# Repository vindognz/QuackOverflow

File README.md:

# QuackOverflow

A wirelessly-charged LED rubber duck for debugging. Custom PCB with RGB LEDs and rechargeable battery fits inside a Kmart duck. Charges on a 3D-printed "DEBUGGING IN PROGRESS" stand. Because explaining your code to a glowing duck is more fun than regular rubber duck debugging.

## Features
- 5x RGB LEDs
- Wireless Qi charging
- Auto-sleep when on charging pad
- Low battery warning (red flash)
- Custom PCB fits inside $2 Kmart duck

## Hardware
- ESP32-C3 microcontroller
- WS2812B RGB LEDs
- LiPo battery with Qi charging
- Custom PCB
- 3D printed charging base

## The Story
Rubber duck debugging is a real technique where programmers explain their code line-by-line to an inanimate object (traditionally a rubber duck) to help spot bugs. I was gifted this duck as a coding companion for my birthday. I always imagined it glowing for those 2am debugging sessions. This project aims to make that dream a reality.

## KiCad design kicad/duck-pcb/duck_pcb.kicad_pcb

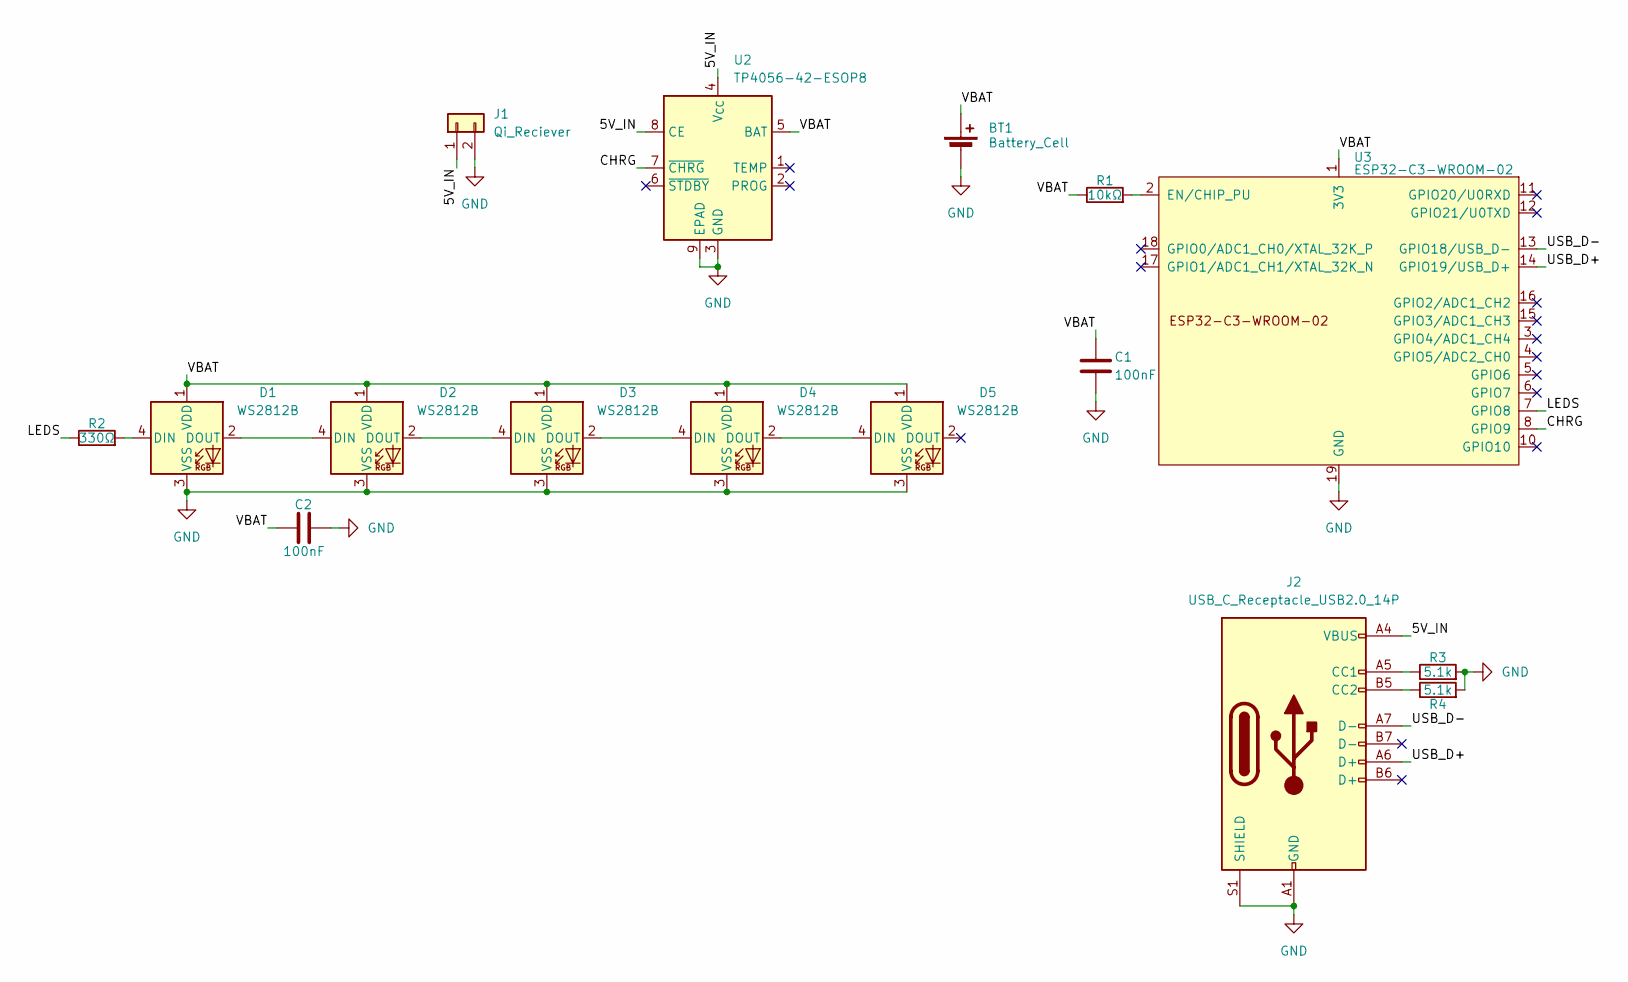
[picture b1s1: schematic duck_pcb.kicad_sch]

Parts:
BT1: Battery_Cell; PinHeader_1x02_P1.00mm_Vertical
C1, C2: 100nF; C_1206_3216Metric_Pad1.33x1.80mm_HandSolder
D1, D2, D3, D4, D5: WS2812B; LED_WS2812B_PLCC4_5.0x5.0mm_P3.2mm
J1: Qi_Reciever; PinHeader_1x02_P1.00mm_Vertical
J2: USB_C_Receptacle_USB2.0_14P; USB_C_Receptacle_HRO_TYPE-C-31-M-12
R1: 10kΩ; R_1206_3216Metric_Pad1.30x1.75mm_HandSolder
R2: 330Ω; R_1206_3216Metric_Pad1.30x1.75mm_HandSolder
R3, R4: 5.1k; R_1206_3216Metric_Pad1.30x1.75mm_HandSolder
U2: TP4056-42-ESOP8; SOIC-8-1EP_3.9x4.9mm_P1.27mm_EP2.41x3.3mm_ThermalVias
U3: ESP32-C3-WROOM-02

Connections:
/5V_IN: J1.1, J2.A4 (VBUS), J2.A9 (VBUS), J2.B4 (VBUS), J2.B9 (VBUS), U2.4 (V_{CC}), U2.8 (CE)
/CHRG: U2.7 (~CHRG), U3.8 (GPIO9)
/LEDS: R2.1, U3.7 (GPIO8)
/USB_D+: J2.A6 (D+), U3.14 (GPIO19/USB_D+)
/USB_D-: J2.A7 (D-), U3.13 (GPIO18/USB_D-)
/VBAT: BT1.1 (+), C1.1, C2.1, D1.1 (VDD), D2.1 (VDD), D3.1 (VDD), D4.1 (VDD), D5.1 (VDD), R1.1, U2.5 (BAT), U3.1 (3V3)
GND: BT1.2 (-), C1.2, C2.2, D1.3 (VSS), D2.3 (VSS), D3.3 (VSS), D4.3 (VSS), D5.3 (VSS), J1.2, J2.A1 (GND), J2.A12 (GND), J2.B1 (GND), J2.B12 (GND), J2.S1 (SHIELD), R3.2, R4.2, U2.3 (GND), U2.9 (EPAD), U3.9 (GND), U3.19 (GND)
unnamed: D1.4 (DIN), R2.2
unnamed: D1.2 (DOUT), D2.4 (DIN)
unnamed: D2.2 (DOUT), D3.4 (DIN)
unnamed: D3.2 (DOUT), D4.4 (DIN)
unnamed: D4.2 (DOUT), D5.4 (DIN)
unnamed: J2.A5 (CC1), R3.1
unnamed: J2.B5 (CC2), R4.1
unnamed: R1.2, U3.2 (EN/CHIP_PU)

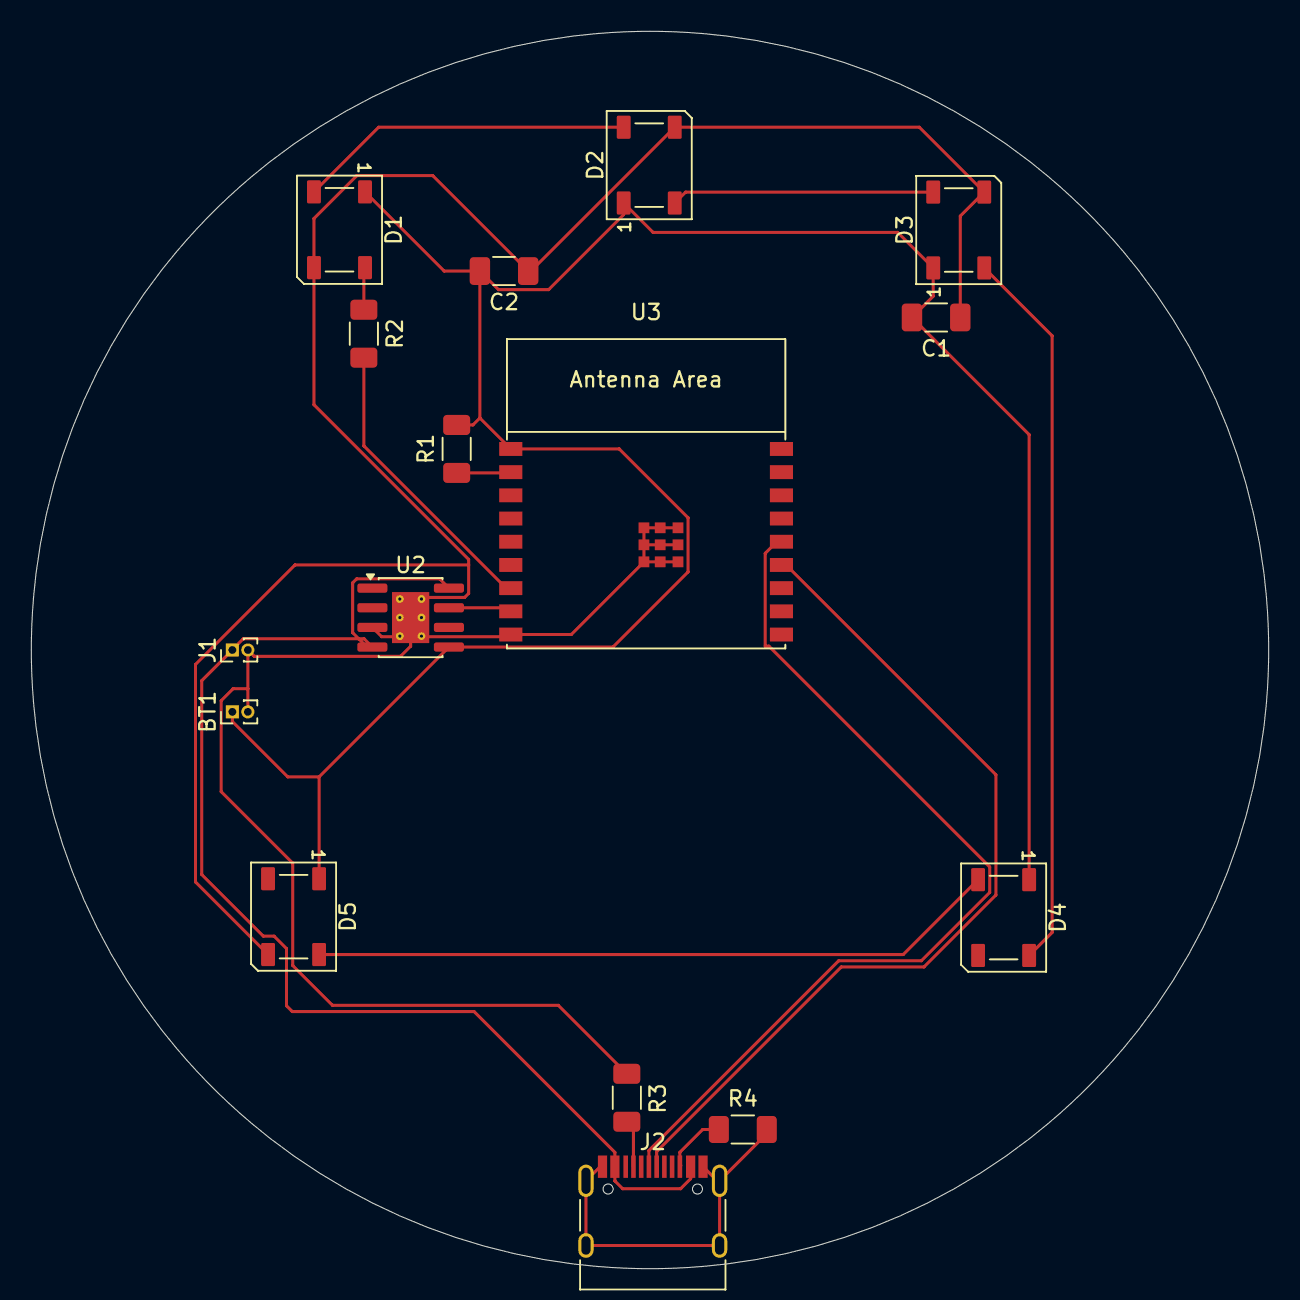
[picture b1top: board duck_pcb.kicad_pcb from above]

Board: 2 copper layers, 80.0 x 80.0 mm, 16 parts (0 on the bottom side), 15 nets.

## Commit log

2025-10-15 The Start...
2025-10-15 The Scope.
2025-10-17 schematic done
2025-10-17 PCB\!\!\!
2025-10-29 renamed pcb cuz i realized i needed to make another
2025-10-29 Revert "renamed pcb cuz i realized i needed to make another"
    This reverts commit 06b52c8c19761527b94a53c6af2c4550971bfb81.
2025-10-29 seperate kicad projects
2025-10-29 holy moly i almost lost everything
